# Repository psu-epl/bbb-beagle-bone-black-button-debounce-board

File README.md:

# bbb-beagle-bone-black-button-debounce-board
Beagle Bone Black Button deBounce Board

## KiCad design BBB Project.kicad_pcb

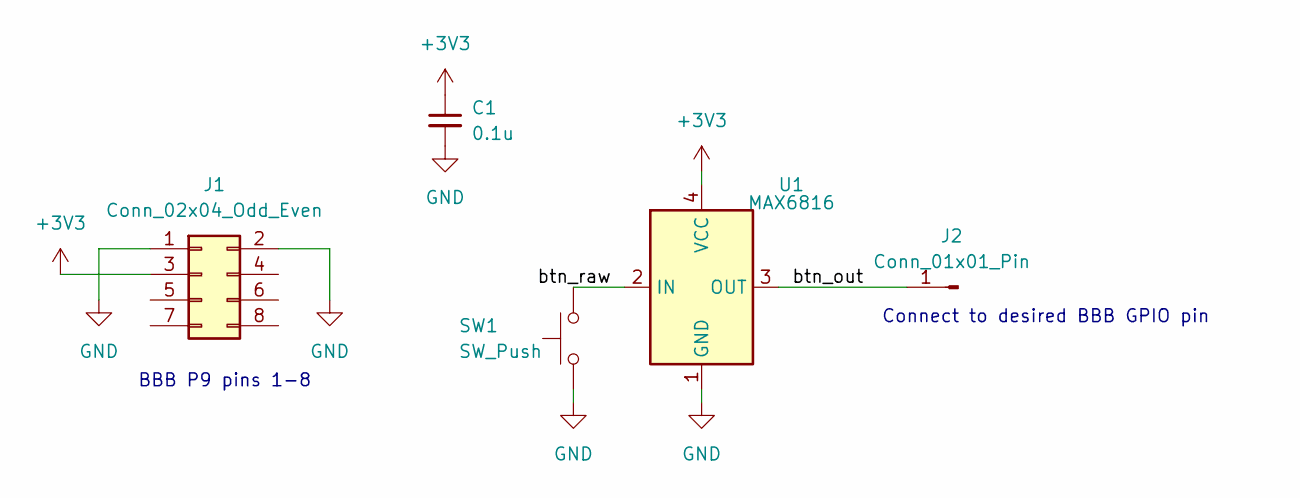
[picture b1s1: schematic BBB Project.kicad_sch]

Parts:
C1: 0.1u; C_0805_2012Metric
J1: Conn_02x04_Odd_Even; PinHeader_2x04_P2.54mm_Vertical
J2: Conn_01x01_Pin; SolderWire-0.25sqmm_1x01_D0.65mm_OD2mm_Relief2x
SW1: SW_Push; SW_Push_1P1T_NO_6x6mm_H9.5mm
U1: MAX6816; SOT-143

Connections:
+3V3: C1.1, J1.3, U1.4 (VCC)
/btn_out: J2.1, U1.3 (OUT)
/btn_raw: SW1.2, U1.2 (IN)
GND: C1.2, J1.1, J1.2, SW1.1, U1.1 (GND)

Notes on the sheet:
BBB P9 pins 1-8
Connect to desired BBB GPIO pin

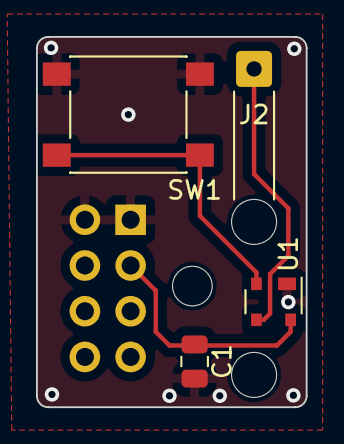
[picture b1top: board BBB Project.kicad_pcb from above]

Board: 2 copper layers, 15.0 x 20.6 mm, 5 parts (1 on the bottom side), 4 nets.

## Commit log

2023-12-07 Added board
2024-01-23 Fixed voltage and verified board
2024-01-23 Roy approves
